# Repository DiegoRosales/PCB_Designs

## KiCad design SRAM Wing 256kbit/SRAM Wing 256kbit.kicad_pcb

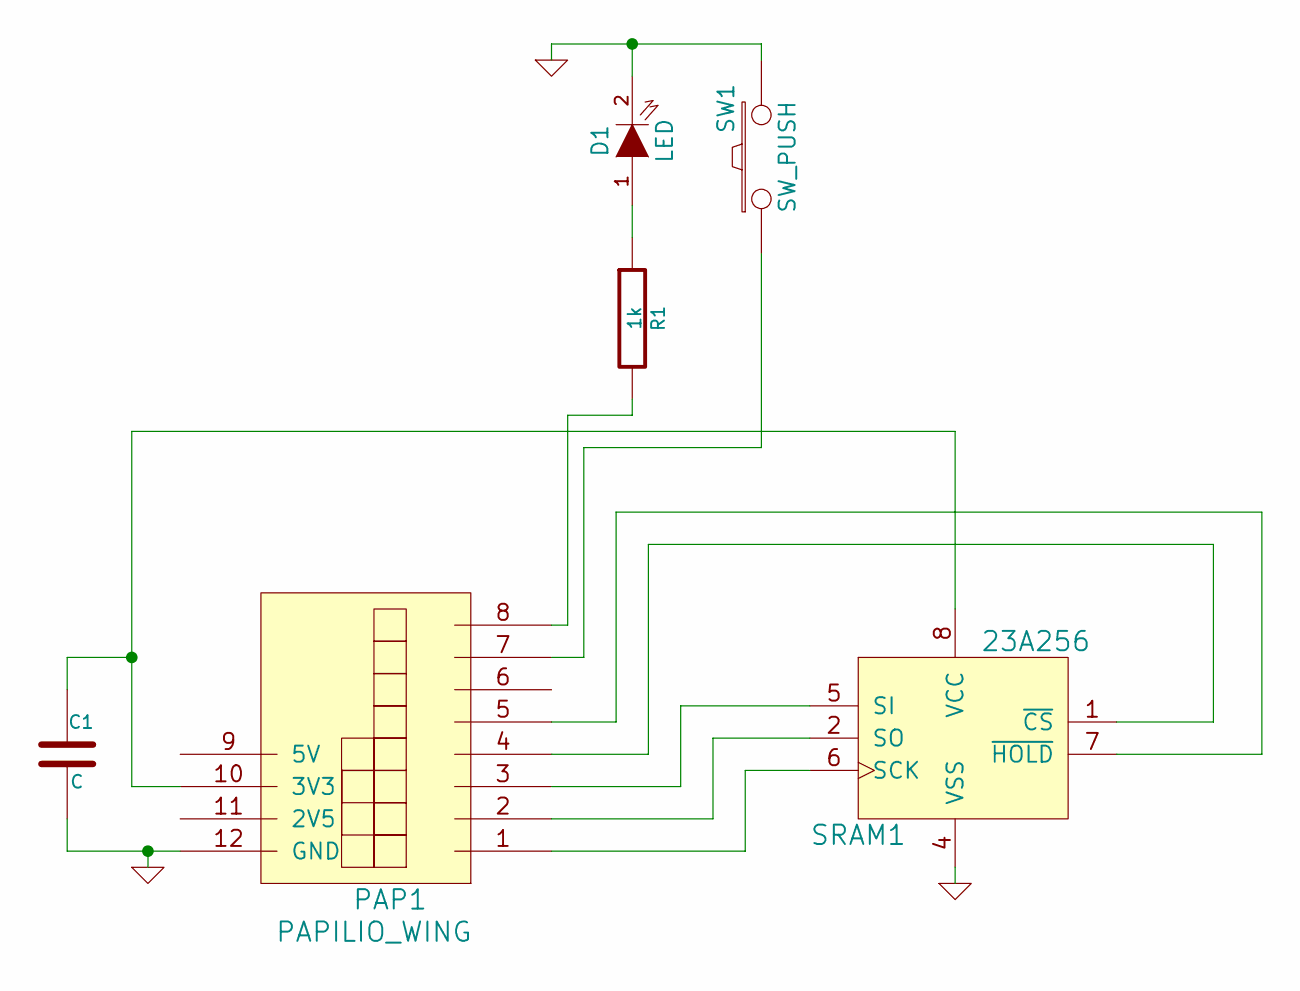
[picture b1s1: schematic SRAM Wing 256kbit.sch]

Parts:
C1: C
D1: LED
PAP1: PAPILIO_WING
R1: 1k
SRAM1: 23A256
SW1: SW_PUSH

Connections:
GND: C1.2, D1.2 (K), PAP1.12 (GND), SRAM1.4 (VSS), SW1.2
unnamed: D1.1 (A), R1.1
unnamed: C1.1, PAP1.10 (3V3), SRAM1.8 (VCC)
unnamed: PAP1.5, SRAM1.7 (~HOLD)
unnamed: PAP1.7, SW1.1
unnamed: PAP1.8, R1.2
unnamed: PAP1.3, SRAM1.5 (SI)
unnamed: PAP1.1, SRAM1.6 (SCK)
unnamed: PAP1.2, SRAM1.2 (SO)
unnamed: PAP1.4, SRAM1.1 (~CS)

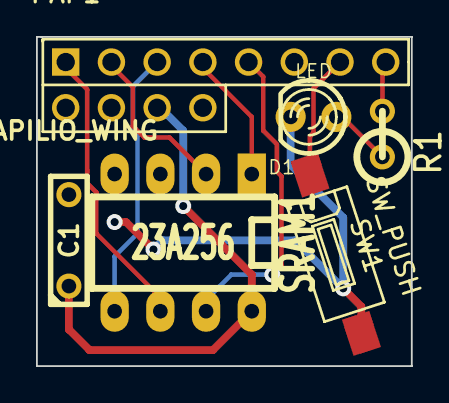
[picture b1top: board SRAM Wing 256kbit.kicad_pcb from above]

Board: 2 copper layers, 20.8 x 18.3 mm, 6 parts (0 on the bottom side), 10 nets.

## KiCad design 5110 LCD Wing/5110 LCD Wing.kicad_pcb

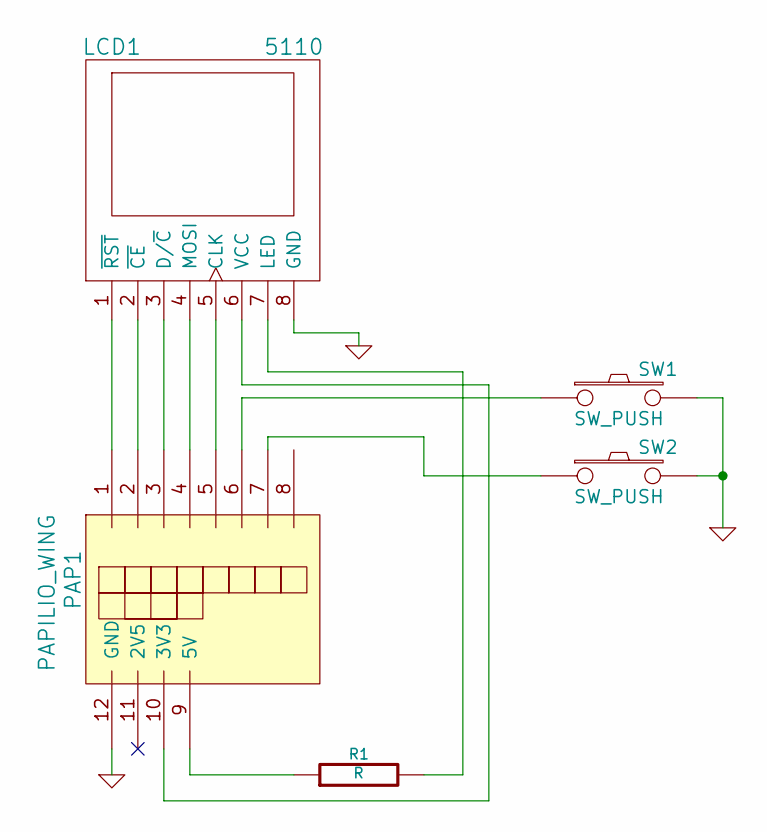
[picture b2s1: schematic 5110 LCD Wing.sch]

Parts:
LCD1: 5110
PAP1: PAPILIO_WING
R1: R
SW1, SW2: SW_PUSH

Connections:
GND: LCD1.8 (GND), PAP1.12 (GND), SW1.2, SW2.2
unnamed: PAP1.7, SW2.1
unnamed: LCD1.4 (MOSI), PAP1.4
unnamed: LCD1.5 (CLK), PAP1.5
unnamed: PAP1.9 (5V), R1.1
unnamed: LCD1.7 (LED), R1.2
unnamed: LCD1.6 (VCC), PAP1.10 (3V3)
unnamed: PAP1.6, SW1.1
unnamed: LCD1.3 (D/~C), PAP1.3
unnamed: LCD1.2 (~CE), PAP1.2
unnamed: LCD1.1 (~RST), PAP1.1

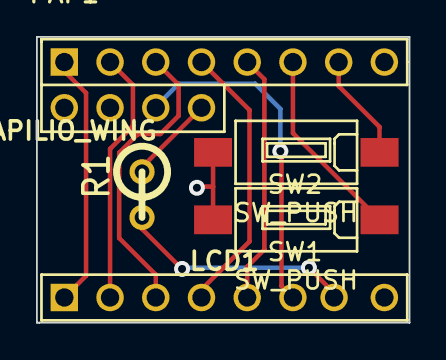
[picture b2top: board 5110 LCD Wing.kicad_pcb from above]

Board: 2 copper layers, 20.7 x 15.9 mm, 5 parts (0 on the bottom side), 11 nets.

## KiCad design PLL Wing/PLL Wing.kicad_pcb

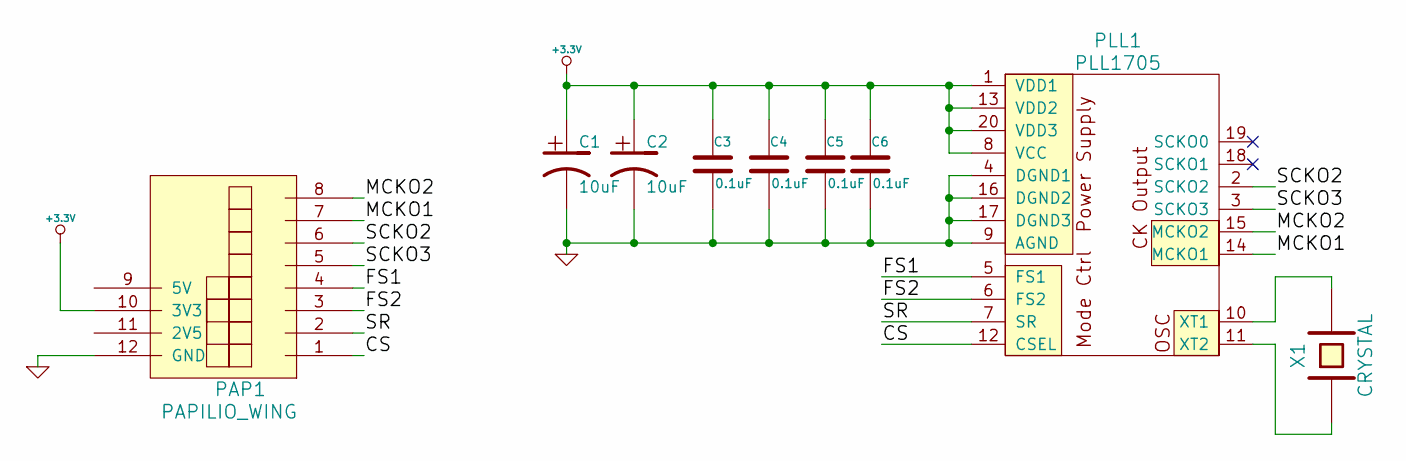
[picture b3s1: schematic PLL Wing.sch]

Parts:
C1, C2: 10uF
C3, C4, C5, C6: 0.1uF
PAP1: PAPILIO_WING
PLL1: PLL1705
X1: CRYSTAL

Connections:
+3.3V: C1.1, C2.1, C3.1, C4.1, C5.1, C6.1, PAP1.10 (3V3), PLL1.1 (VDD1), PLL1.8 (VCC), PLL1.13 (VDD2), PLL1.20 (VDD3)
/CS: PAP1.1, PLL1.12 (CSEL)
/FS1: PAP1.4, PLL1.5 (FS1)
/FS2: PAP1.3, PLL1.6 (FS2)
/MCKO1: PAP1.7, PLL1.14 (MCKO1)
/MCKO2: PAP1.8, PLL1.15 (MCKO2)
/SCKO2: PAP1.6, PLL1.2 (SCKO2)
/SCKO3: PAP1.5, PLL1.3 (SCKO3)
/SR: PAP1.2, PLL1.7 (SR)
GND: C1.2, C2.2, C3.2, C4.2, C5.2, C6.2, PAP1.12 (GND), PLL1.4 (DGND1), PLL1.9 (AGND), PLL1.16 (DGND2), PLL1.17 (DGND3)
unnamed: PLL1.10 (XT1), X1.2
unnamed: PLL1.11 (XT2), X1.1

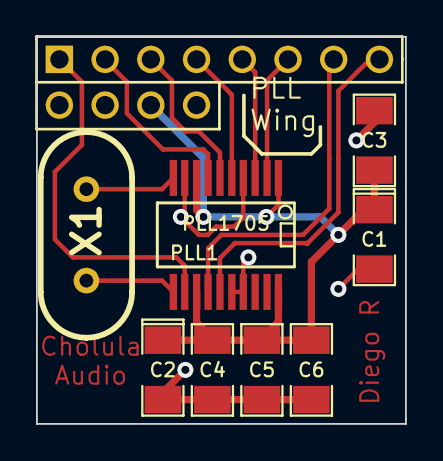
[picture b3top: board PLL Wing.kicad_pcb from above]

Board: 2 copper layers, 20.5 x 21.5 mm, 9 parts (0 on the bottom side), 12 nets.

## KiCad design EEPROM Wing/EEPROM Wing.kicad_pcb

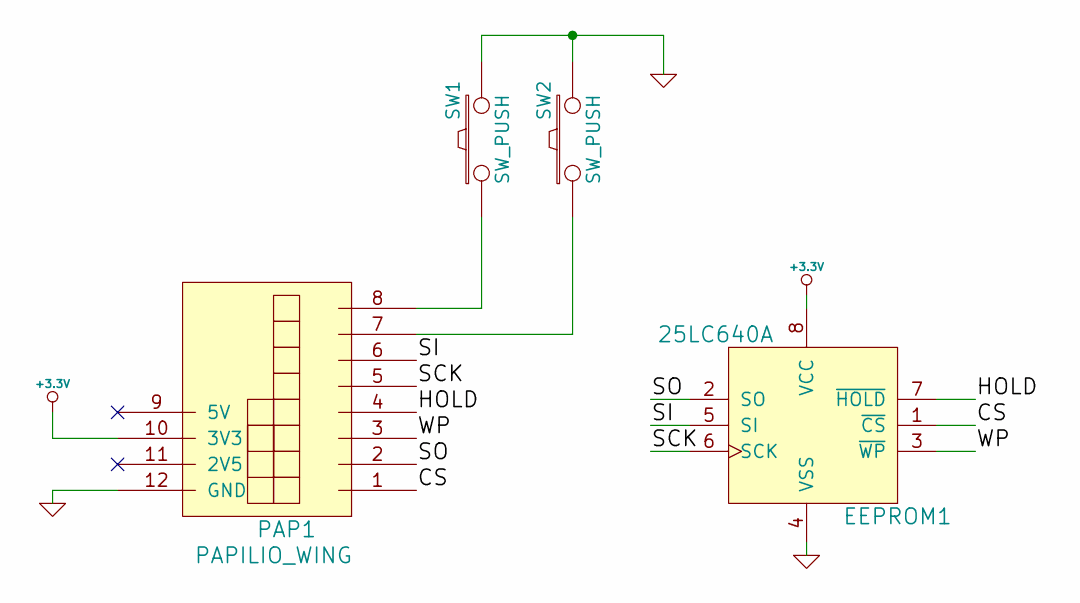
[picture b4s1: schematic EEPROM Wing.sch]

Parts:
EEPROM1: 25LC640A
PAP1: PAPILIO_WING
SW1, SW2: SW_PUSH

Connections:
+3.3V: EEPROM1.8 (VCC), PAP1.10 (3V3)
/CS: EEPROM1.1 (~CS), PAP1.1
/HOLD: EEPROM1.7 (~HOLD), PAP1.4
/SCK: EEPROM1.6 (SCK), PAP1.5
/SI: EEPROM1.5 (SI), PAP1.6
/SO: EEPROM1.2 (SO), PAP1.2
/WP: EEPROM1.3 (~WP), PAP1.3
GND: EEPROM1.4 (VSS), PAP1.12 (GND), SW1.2, SW2.2
unnamed: PAP1.7, SW2.1
unnamed: PAP1.8, SW1.1

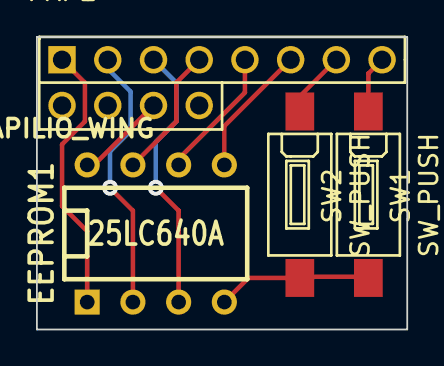
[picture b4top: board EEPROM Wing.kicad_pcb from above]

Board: 2 copper layers, 20.6 x 16.3 mm, 4 parts (0 on the bottom side), 10 nets.

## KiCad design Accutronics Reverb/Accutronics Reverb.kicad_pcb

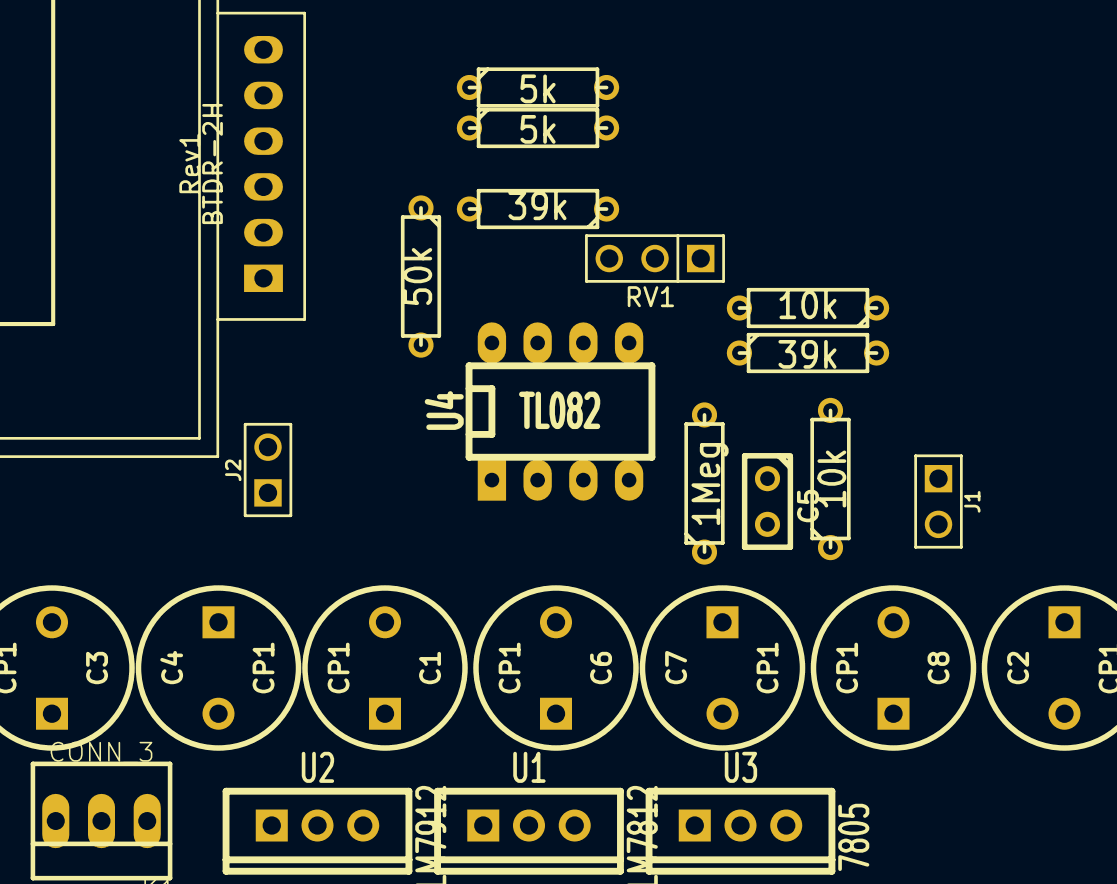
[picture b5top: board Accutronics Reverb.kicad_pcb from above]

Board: 2 copper layers, 25 parts (0 on the bottom side), 16 nets, no tracks yet.

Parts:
C1, C2, C3, C4, C6, C7, C8: CP1; C2V8
C5: 22nF; C1
J1, J2: JACK_MN; PIN_ARRAY_2X1
K1: CONN_3; PINHEAD1-3
R1, R6: 10k; R3
R2: 1Meg; R3
R3, R4: 5k; R3
R5, R8: 39k; R3
R7: 50k; R3
RV1: 50k; PIN_ARRAY_3X1
Rev1: BTDR-2H; Accutronics1
U1: LM7812; TO220_VERT
U2: LM7912; TO220_VERT
U3: 7805; TO220_VERT
U4: TL082; DIP-8__300_ELL

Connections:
+5V: C8.1, Rev1.1
+12V: C6.1, U4.8
/IN: J1.2, R1.1, R6.1
/OUT: J2.2, R7.2, U4.7
GND: C1.2, C2.1, C3.2, C4.1, C6.2, C7.1, C8.2, J1.1, J2.1, K1.2, R8.2, RV1.3, Rev1.2, Rev1.4, U4.3, U4.4
unnamed: C1.1, C3.1, K1.3
unnamed: C2.2, C4.2, K1.1
unnamed: R3.1, Rev1.6
unnamed: R4.1, Rev1.5
unnamed: R3.2, R4.2, RV1.1
unnamed: C5.1, R1.2
unnamed: C5.2, R2.1, U4.2
unnamed: R2.2, Rev1.3, U4.1
unnamed: R5.1, RV1.2
unnamed: R5.2, R7.1, U4.6
unnamed: R6.2, R8.1, U4.5

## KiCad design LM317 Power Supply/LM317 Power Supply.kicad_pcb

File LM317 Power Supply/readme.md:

#**LM317 Power Supply with split supply**
Rev 1.3
---
This is a simple LM317 variable power supply with an extra circuit that creates a split supply to power opamps and stuff. It's *theoretically* capable of sourcing like 1 amp, but I haven't tested that yet. To generate the split supply I used a voltage divider and an Op Amp from Linear Technologies called LT1206 as a buffer. Here is the link of the article that explains how to generate split supplies with a Virtual Ground. [Virtual Ground Circuits](http://tangentsoft.net/elec/vgrounds.html)

Here are some pics

---

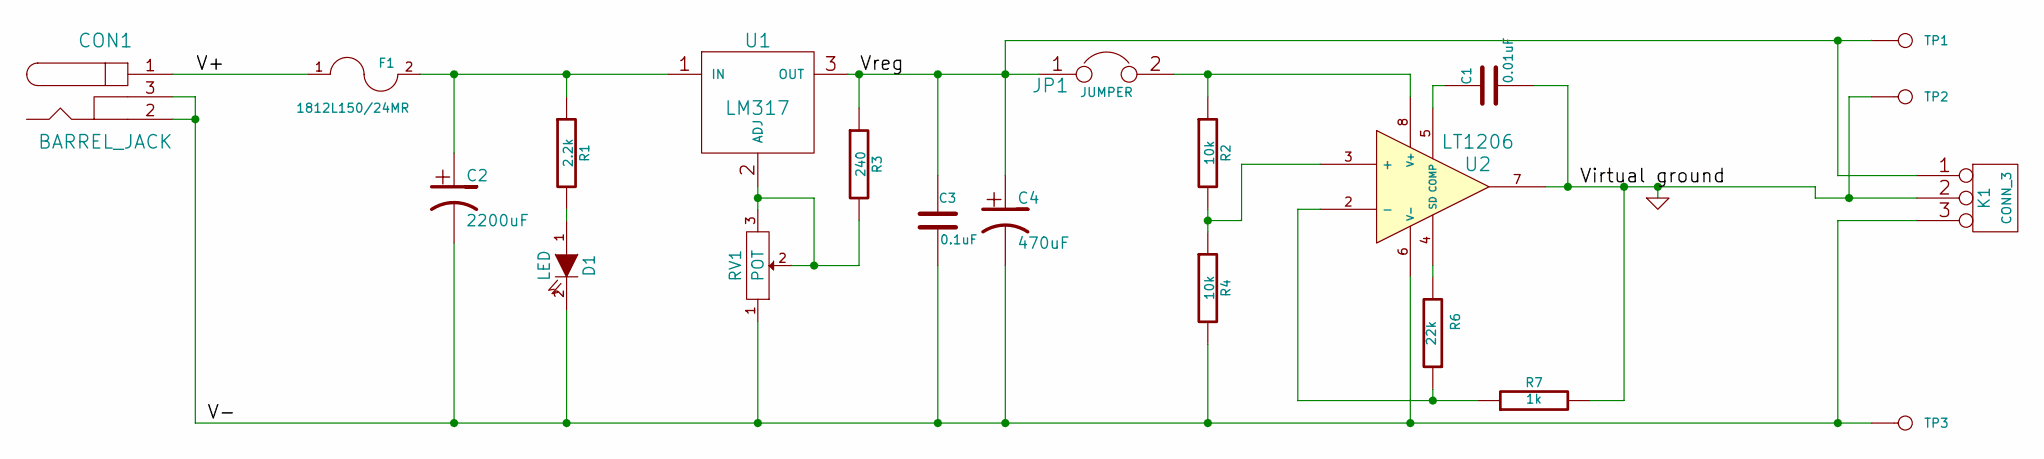
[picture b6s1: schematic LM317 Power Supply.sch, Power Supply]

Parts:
C1: 0.01uF
C2: 2200uF
C3: 0.1uF
C4: 470uF
CON1: BARREL_JACK
D1: LED
F1: 1812L150/24MR
JP1: JUMPER
K1: CONN_3
R1: 2.2k
R2, R4: 10k
R3: 240
R6: 22k
R7: 1k
RV1: POT
TP1, TP2, TP3: CONN_1
U1: LM317
U2: LT1206

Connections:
/V+: CON1.1, F1.1
/V-: C2.2, C3.2, C4.2, CON1.2, CON1.3, D1.2 (K), K1.3, R4.2, RV1.1, TP3.1, U2.6 (V-)
/Vreg: C3.1, C4.1, JP1.1, K1.1, R3.1, TP1.1, U1.3 (OUT)
GND: C1.2, K1.2 (PM), R7.2, TP2.1, U2.7
unnamed: R2.2, R4.1, U2.3 (+)
unnamed: R6.2, U2.4 (SD)
unnamed: JP1.2, R2.1, U2.8 (V+)
unnamed: C1.1, U2.5 (COMP)
unnamed: R6.1, R7.1, U2.2 (-)
unnamed: D1.1 (A), R1.2
unnamed: R3.2, RV1.2, RV1.3, U1.2 (ADJ)
unnamed: C2.1, F1.2, R1.1, U1.1 (IN)

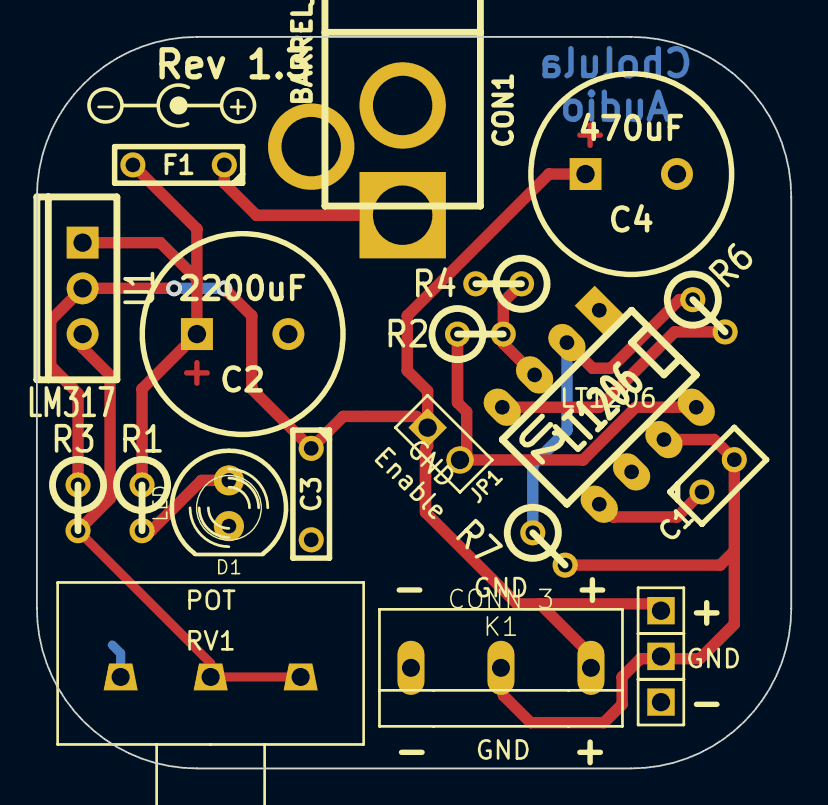
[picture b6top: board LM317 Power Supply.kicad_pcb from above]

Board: 2 copper layers, 41.9 x 40.6 mm, 21 parts (0 on the bottom side), 12 nets.

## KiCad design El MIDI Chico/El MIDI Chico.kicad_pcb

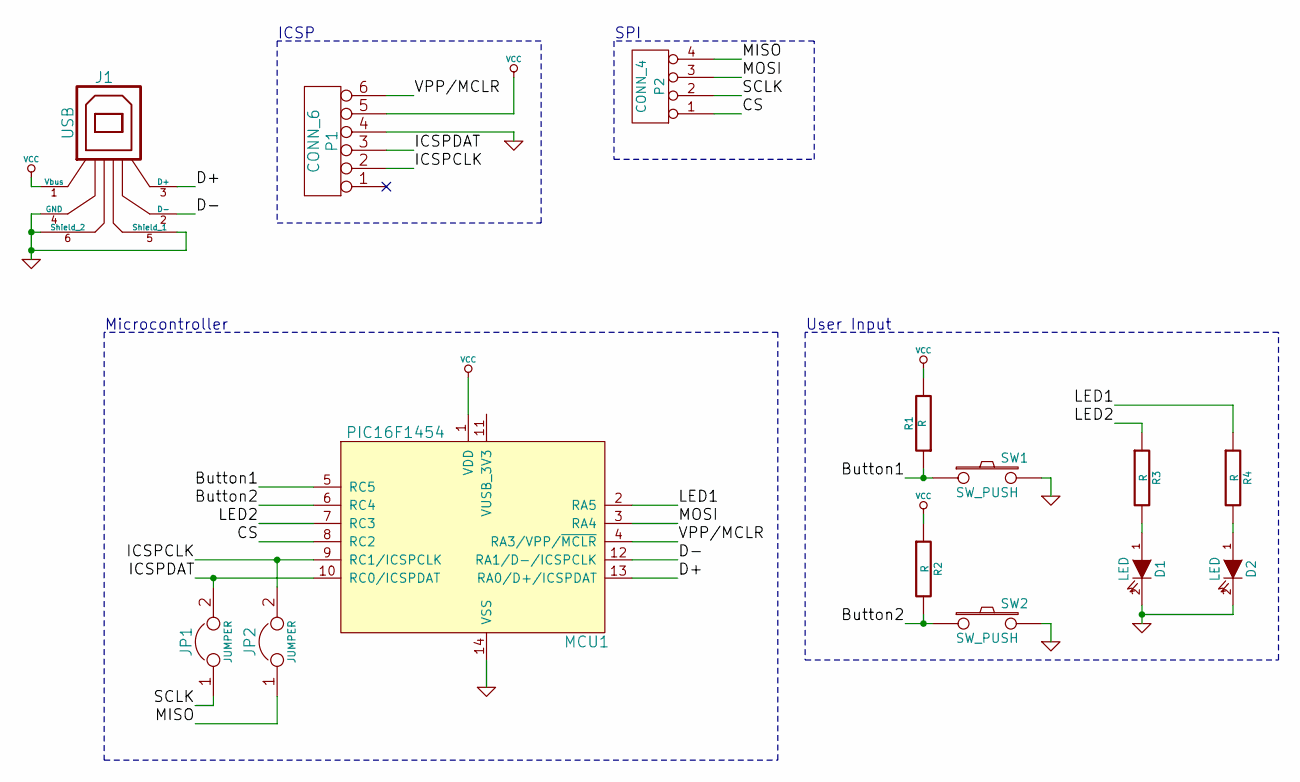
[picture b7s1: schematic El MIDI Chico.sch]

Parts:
D1, D2: LED
J1: USB
JP1, JP2: JUMPER
MCU1: PIC16F1454
P1: CONN_6
P2: CONN_4
R1, R2, R3, R4: R
SW1, SW2: SW_PUSH

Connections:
/Button1: MCU1.5 (RC5), R1.1, SW1.1
/Button2: MCU1.6 (RC4), R2.2, SW2.1
/CS: MCU1.8 (RC2), P2.1
/D+: J1.3 (D+), MCU1.13 (RA0/D+/ICSPDAT)
/D-: J1.2 (D-), MCU1.12 (RA1/D-/ICSPCLK)
/ICSPCLK: JP2.2, MCU1.9 (RC1/ICSPCLK), P1.2
/ICSPDAT: JP1.2, MCU1.10 (RC0/ICSPDAT), P1.3
/LED1: MCU1.2 (RA5), R4.1
/LED2: MCU1.7 (RC3), R3.1
/MISO: JP2.1, P2.4
/MOSI: MCU1.3 (RA4), P2.3
/SCLK: JP1.1, P2.2
/VPP/MCLR: MCU1.4 (RA3/VPP/~MCLR), P1.6
GND: D1.2 (K), D2.2 (K), J1.4 (GND), J1.5 (Shield_1), J1.6 (Shield_2), MCU1.14 (VSS), P1.4, SW1.2, SW2.2
unnamed: D1.1 (A), R3.2
unnamed: D2.1 (A), R4.2
VCC: J1.1 (Vbus), MCU1.1 (VDD), P1.5, R1.2, R2.1

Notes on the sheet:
ICSP
SPI
User Input
Microcontroller

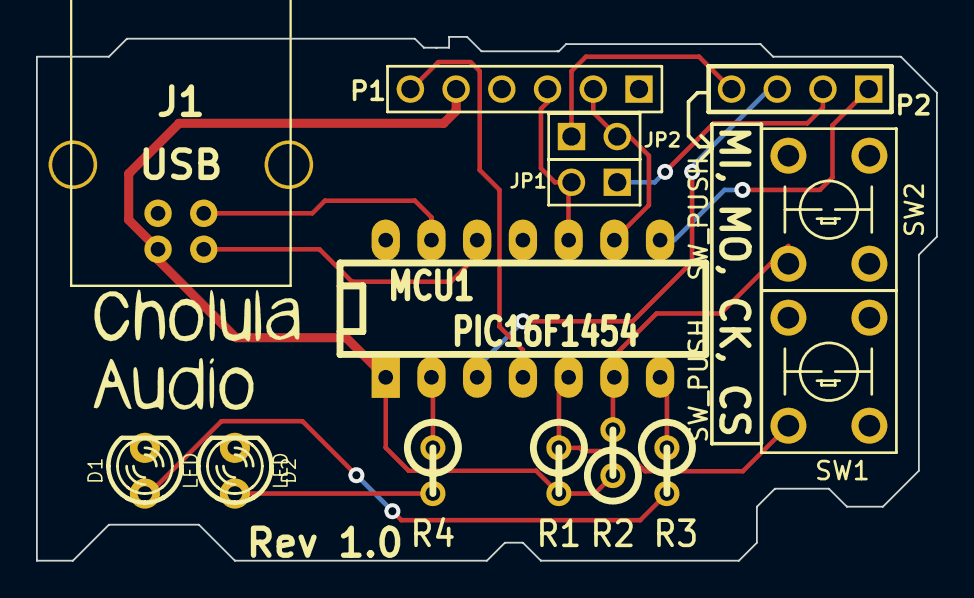
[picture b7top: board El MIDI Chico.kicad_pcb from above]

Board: 2 copper layers, 50.0 x 29.1 mm, 14 parts (0 on the bottom side), 17 nets.

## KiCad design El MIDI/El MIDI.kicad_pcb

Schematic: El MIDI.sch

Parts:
ADC1: MCP3004
D1, D2, D3, D4, D5, D6, D7, D8: LED
J1: USB
JP1, JP2: JUMPER
MCU1: PIC16F1454
P1: CONN_6
R1, R2, R3, R4, R5, R6, R7, R8: R
R9, R10, R11, R12, R13, R14, R15, R16: 1k
RV1, RV2, RV3, RV4: POT
SW1, SW2, SW3, SW4: SWITCH_INV
SW5, SW6, SW7, SW8: PUSHBUTTON
U1, U2: MCP23S08

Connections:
/Btn1: R5.1, SW5.1, SW5.2, U1.10 (GP0)
/Btn2: R6.1, SW6.1, SW6.2, U1.13 (GP3)
/Btn3: R7.1, SW7.1, SW7.2, U1.12 (GP2)
/Btn4: R8.1, SW8.1, SW8.2, U1.11 (GP1)
/CS_ADC: ADC1.8 (SHDN/~CS), MCU1.8 (RC2)
/CS_IOEXP: MCU1.7 (RC3), U1.7 (~CS), U2.7 (~CS)
/D+: J1.3 (D+), MCU1.13 (RA0/D+/ICSPDAT)
/D-: J1.2 (D-), MCU1.12 (RA1/D-/ICSPCLK)
/ICSPCLK: JP2.2, MCU1.9 (RC1/ICSPCLK), P1.2
/ICSPDAT: JP1.2, MCU1.10 (RC0/ICSPDAT), P1.3
/INT_IOEXP: MCU1.6 (RC4), U1.8 (INT)
/Knob1: ADC1.1 (CH0), RV1.2
/Knob2: ADC1.2 (CH1), RV2.2
/Knob3: ADC1.3 (CH2), RV3.2
/Knob4: ADC1.4 (CH3), RV4.2
/LED1: R9.1, U2.14 (GP4)
/LED2: R10.1, U2.15 (GP5)
/LED3: R11.1, U2.16 (GP6)
/LED4: R12.1, U2.17 (GP7)
/LED5: R13.1, U2.13 (GP3)
/LED6: R14.1, U2.12 (GP2)
/LED7: R15.1, U2.11 (GP1)
/LED8: R16.1, U2.10 (GP0)
/MISO: ADC1.10 (DOUT), JP2.1, U1.3 (SO), U2.3 (SO)
/MOSI: ADC1.9 (DIN), MCU1.3 (RA4), U1.2 (SI), U2.2 (SI)
/RESET_IOEXP: MCU1.5 (RC5), U1.6 (~RESET), U2.6 (~RESET)
/SCLK: ADC1.11 (CLK), JP1.1, U1.1 (SCK), U2.1 (SCK)
/Switch1: R1.1, U1.14 (GP4)
/Switch2: R2.1, U1.15 (GP5)
/Switch3: R3.1, U1.16 (GP6)
/Switch4: R4.1, U1.17 (GP7)
/VPP/MCLR: MCU1.4 (RA3/VPP/~MCLR), P1.6
GND: ADC1.7 (DGND), ADC1.12 (AGND), D1.2 (K), D2.2 (K), D3.2 (K), D4.2 (K), D5.2 (K), D6.2 (K), D7.2 (K), D8.2 (K), J1.4 (GND), J1.5 (Shield_1), J1.6 (Shield_2), MCU1.14 (VSS), P1.4, RV1.1, RV2.1, RV3.1, RV4.1, SW1.3, SW2.3, SW3.3, SW4.3, SW5.3, SW5.4, SW6.3, SW6.4, SW7.3, SW7.4, SW8.3, SW8.4, U1.4 (A1), U1.5 (A0), U1.9 (VSS), U2.9 (VSS)
unnamed: D8.1 (A), R16.2
unnamed: D7.1 (A), R15.2
unnamed: D6.1 (A), R14.2
unnamed: D5.1 (A), R13.2
unnamed: D4.1 (A), R12.2
unnamed: D3.1 (A), R11.2
unnamed: D2.1 (A), R10.2
unnamed: R1.2, SW1.2
unnamed: R2.2, SW2.2
unnamed: R3.2, SW3.2
unnamed: R4.2, SW4.2
unnamed: D1.1 (A), R9.2
VCC: ADC1.13 (VREF), ADC1.14 (VDD), J1.1 (Vbus), MCU1.1 (VDD), P1.5, R5.2, R6.2, R7.2, R8.2, RV1.3, RV2.3, RV3.3, RV4.3, SW1.1, SW2.1, SW3.1, SW4.1, U1.18 (VDD), U2.4 (A1), U2.5 (A0), U2.18 (VDD)

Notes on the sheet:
ICSP

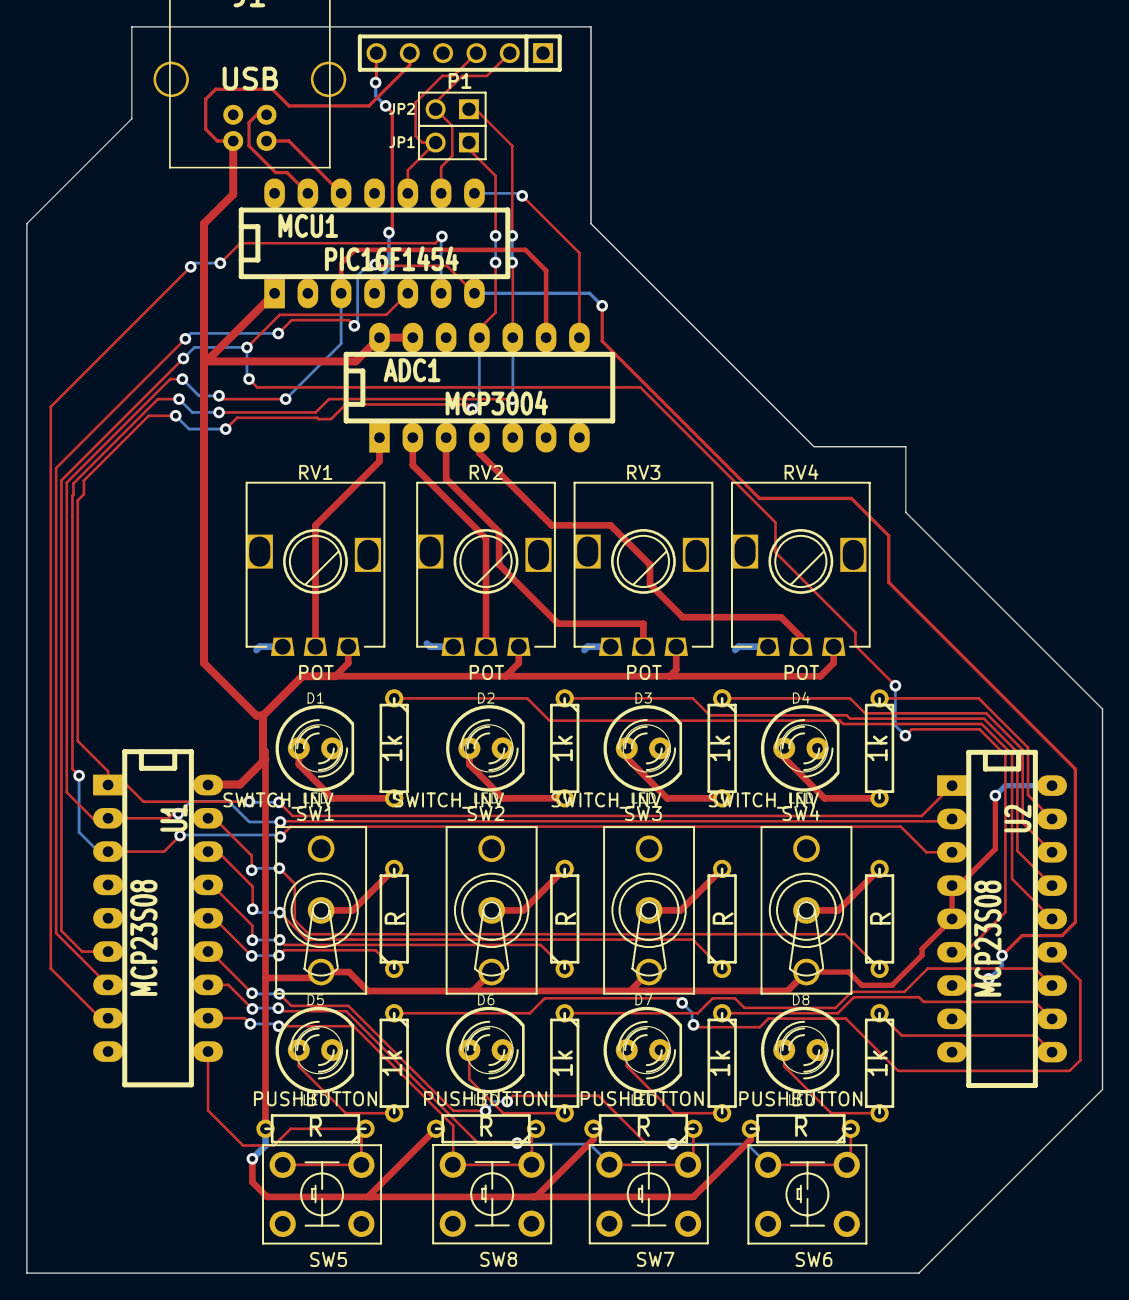
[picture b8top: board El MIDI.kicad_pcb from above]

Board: 2 copper layers, 82.0 x 95.0 mm, 44 parts (0 on the bottom side), 46 nets.

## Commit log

2014-07-07 Created repository
    Created repository
2014-07-07 Added DAC Wing
    DAC Wing for the Papilio FPGA Platform. It's based on the MAX5556 DAC.
2014-07-30 Added VHDL Examples
    Added VHDL Examples (not finished)
2014-07-30 stackdump
    stackdump
2014-08-08 Arduino Header MegaWing
    Arduino Header MegaWing
2014-08-09 Quetzalcoatl V1.0
    Digital Snake Wing
2014-08-17 Readme
    Readme
2014-08-17 Readme
2014-09-02 DAC and CODEC Wing
    DAC and CODEC Wing
2014-09-07 More stuff
2014-09-07 Created readme
2014-09-15 Power Supply Rev 1.3
    Deleted unnecesary load, fixed potentiometer orientation and other stuff
2014-09-15 El MIDI
2014-09-26 CODEC Wing
2015-02-23 Small wings
